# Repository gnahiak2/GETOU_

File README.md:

# getou_
Its pretty much a hackpad but i made it myself

Here's the Zine!
<div align="center">
  
</div>

( This needs manual review cuz fallout project )

## HOW THIS WAS MADE
Firmware was made in C via qmk, the accompanying app was made in swift with the help of chatgpt

## Here's how to compile and flash the project
1. Clone the source code to your device
```bash
git clone https://github.com/gnahiak2/getou_.git
cd getou_
```

2. Compile firmware
```bash
qmk compile -kb getou_ -km default
```

3. Plug in your USB-C Cable while holding the Boot button (marked B)

4. Drag the .uf2 file into the RP2040 and you're done!

## AI DISCLOSURE
AI was used for QMK

## Images

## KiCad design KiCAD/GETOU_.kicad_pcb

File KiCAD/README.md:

# GETOU_
This is a 12key macropad with a accompanying windows app that can be configured either as a one handed keyboard for gaming, a soundboard or a macropad.

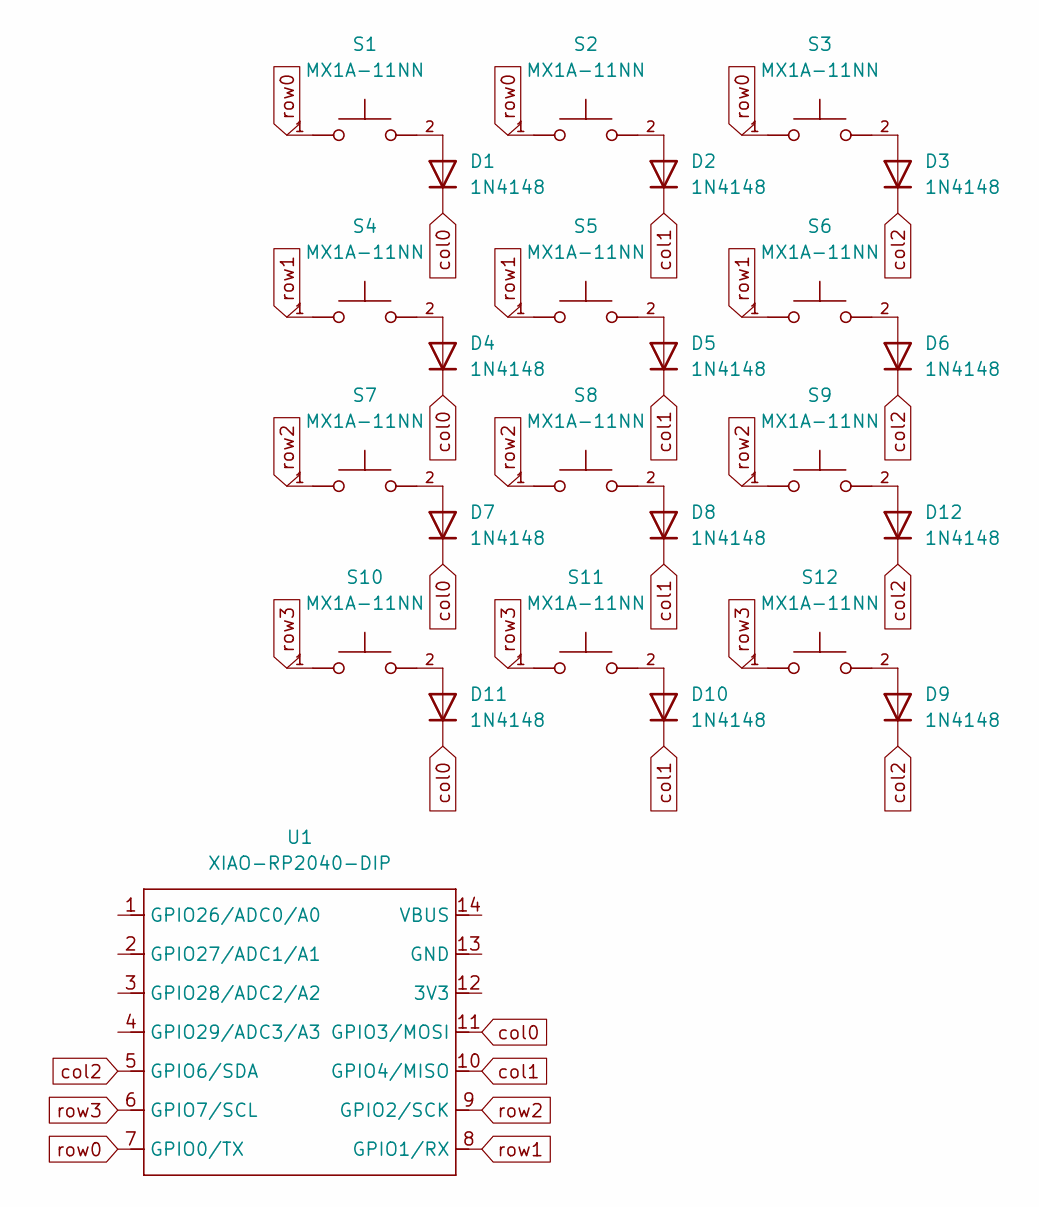
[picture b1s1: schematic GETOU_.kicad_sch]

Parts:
D1, D2, D3, D4, D5, D6, D7, D8, D9, D10, D11, D12: 1N4148; D_DO-35_SOD27_P7.62mm_Horizontal
S1, S2, S3, S4, S5, S6, S7, S8, S9, S10, S11, S12: MX1A-11NN; SW_MX1A-11NN
U1: XIAO-RP2040-DIP

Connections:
unnamed: D1.2 (A), S1.2
unnamed: D2.2 (A), S2.2
unnamed: D3.2 (A), S3.2
unnamed: D4.2 (A), S4.2
unnamed: D5.2 (A), S5.2
unnamed: D6.2 (A), S6.2
unnamed: D7.2 (A), S7.2
unnamed: D8.2 (A), S8.2
unnamed: D9.2 (A), S12.2
unnamed: D10.2 (A), S11.2
unnamed: D11.2 (A), S10.2
unnamed: D12.2 (A), S9.2
col0: D1.1 (K), D4.1 (K), D7.1 (K), D11.1 (K), U1.11 (GPIO3/MOSI)
col1: D2.1 (K), D5.1 (K), D8.1 (K), D10.1 (K), U1.10 (GPIO4/MISO)
col2: D3.1 (K), D6.1 (K), D9.1 (K), D12.1 (K), U1.5 (GPIO6/SDA)
row0: S1.1, S2.1, S3.1, U1.7 (GPIO0/TX)
row1: S4.1, S5.1, S6.1, U1.8 (GPIO1/RX)
row2: S7.1, S8.1, S9.1, U1.9 (GPIO2/SCK)
row3: S10.1, S11.1, S12.1, U1.6 (GPIO7/SCL)

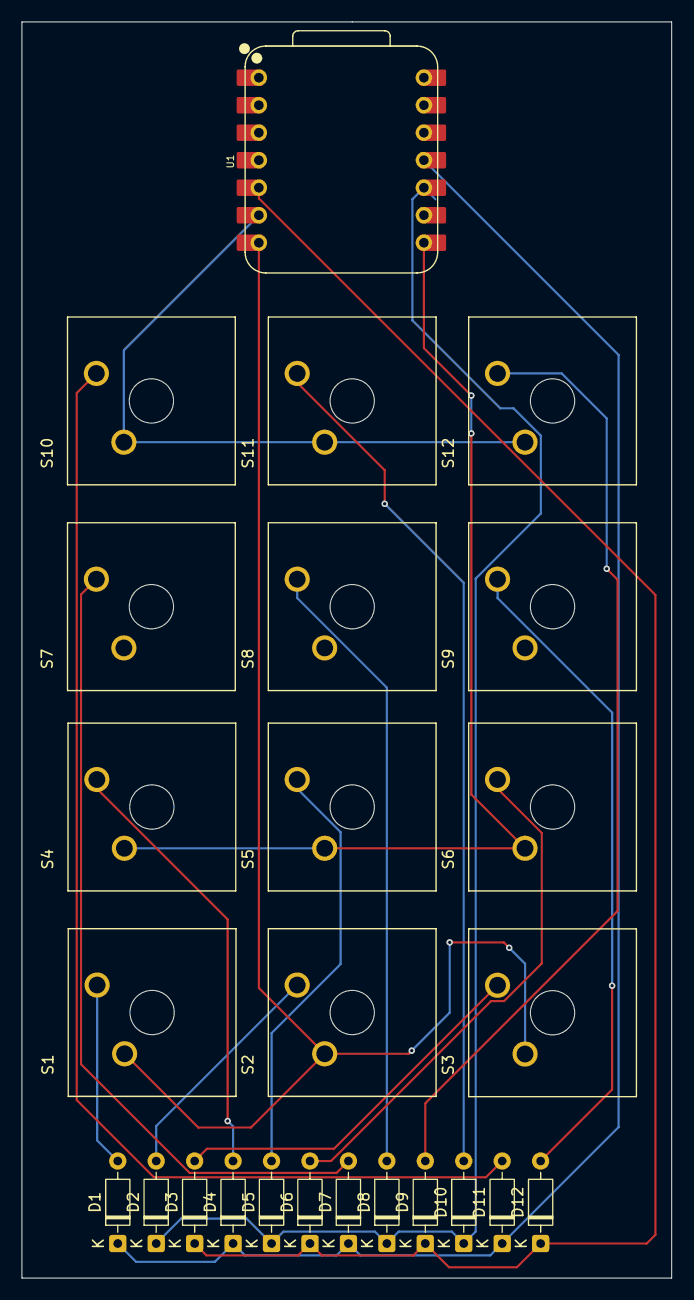
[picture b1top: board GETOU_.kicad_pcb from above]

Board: 2 copper layers, 60.0 x 116.0 mm, 25 parts (0 on the bottom side), 19 nets.

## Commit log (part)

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2026-03-13 Add KiCad files
2026-03-14 Add KB switches and RPI Pico
2026-03-14 Modify Schematic
2026-03-14 Edit PCB
2026-03-15 Update README.md to include project description
2026-03-15 Modify PCB
2026-03-16 This commit moves the KiCAD project files into a new directory named "KiCAD". The original files have been deleted from the root directory and added to the "KiCAD" directory, along with a new .gitign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
2026-03-16 Add Files
2026-03-16 Add and modify files
2026-03-16 Create LICENSE
2026-03-16 Initialize README with project details
    Add project description for GETOU_ macropad.
2026-03-17 add files from CAD and KiCAD directories, remove old files from Fusion and KiCAD backups, and update the main KiCAD PCB and PRL files.
2026-03-17 Create .gitignore for KiCad project
    Add .gitignore file for KiCad project to exclude temporary and backup files.
2026-03-17 Add QMK keyboard definition for GETOU_ under Firmware
2026-03-17 Add GETOU_ QMK keyboard definition
2026-03-18 Deleted files: Firmware/qmk/keyboards/getou_/config.h Firmware/qmk/keyboards/getou_/rules.mk Fusion/PCB.stl
2026-03-20 Add LICENSE file
2026-04-04 Update README.md to clarify macropad functionality
2026-04-04 Add stuff
2026-04-26 Remove unused firmware files and documentation
2026-04-27 Add new keyboard configuration for getou_
    - Created keyboard.json for the getou_ keyboard with specifications including manufacturer, bootloader, and matrix pin configuration.
    - Added default keymap implementation in keymap.c with a simple number layout.
    - Included a readme.md file with project description, maintainer information, build instructions, and bootloader entry methods.
    - Updated KiCAD subproject commit to indicate a dirty state.
2026-04-27 Create .gitignore for KiCad project files
    Add .gitignore file for KiCad project to exclude temporary and backup files.
2026-04-27 Revise README.md with detailed project information
    Expanded project description and features for GETOU_ macropad.
2026-04-27 Fix values in GETOU_ project files for improved accuracy
    - Updated numerical values in GETOU_.kicad_prl to correct component specifications.
    - Adjusted positions of global labels in GETOU_.kicad_sch for better alignment and clarity.
2026-05-04 Modify Files
2026-05-04 Modifiy Files
2026-05-16 Add Zine
2026-05-16 Add image of fully assembled macropad
    Added an image of the fully assembled macropad to the README.
2026-05-16 Add BOM.csv
2026-05-16 Add Purchace Links and Case to BOM.csv
2026-05-17 Update Zine
2026-05-17 Modify Zine
2026-05-17 Modify BOM
2026-05-24 Initial plan
2026-05-24 Add macOS-native GetouCompanion SwiftUI scaffold (profiles + stub device + macro runner)
2026-05-24 Docs: add GetouCompanion build/run instructions (Xcode + xcodebuild + VS Code)
2026-05-24 Add VS Code configuration files and build instructions for GetouCompanion
2026-05-24 Update .gitignore to correctly reference KiCad history and mark subproject as dirty
2026-05-24 Update .gitignore to include trailing slash for KiCad history and mark subproject as dirty
2026-05-24 Remove KiCAD history subproject reference
2026-05-24 Update macOS requirement from 13+ to 14+
2026-05-24 Add asset files for app icon and initial asset catalog structure; remove ProfileDetailView and ProfileStore classes
2026-05-24 Add ProfileDetailView and ProfileStore for managing user profiles
    - Created ProfileDetailView to display detailed information about a selected profile and its associated macros.
    - Implemented ProfileStore to handle loading and saving profiles to a JSON file in the application support directory.
    - Added a new scheme management plist file for user state.
    - Included a .DS_Store file for directory management.
2026-05-26 Replace images with placeholders and descriptions
    Updated image placeholders in README.md with descriptions.
2026-05-29 Update settings and README for project configuration and image display
2026-05-29 Refactor code structure for improved readability and maintainability
2026-06-01 Update KiCAD project settings, add .DS_Store, and implement InputService class
    - Changed active_layer in KiCAD project from 7 to 2 for improved layout management.
    - Added .DS_Store file in Firmware directory to manage Finder settings.
    - Created InputService class in GetouCompanion to handle key press events, with a placeholder for future input simulation.
2026-06-03 Add .gitignore to exclude .DS_Store and .vscode directories
2026-06-03 Remove Visual Studio Code configuration files
